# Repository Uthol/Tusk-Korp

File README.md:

# Tusk Korp
Repo for all of my keyboard designs.

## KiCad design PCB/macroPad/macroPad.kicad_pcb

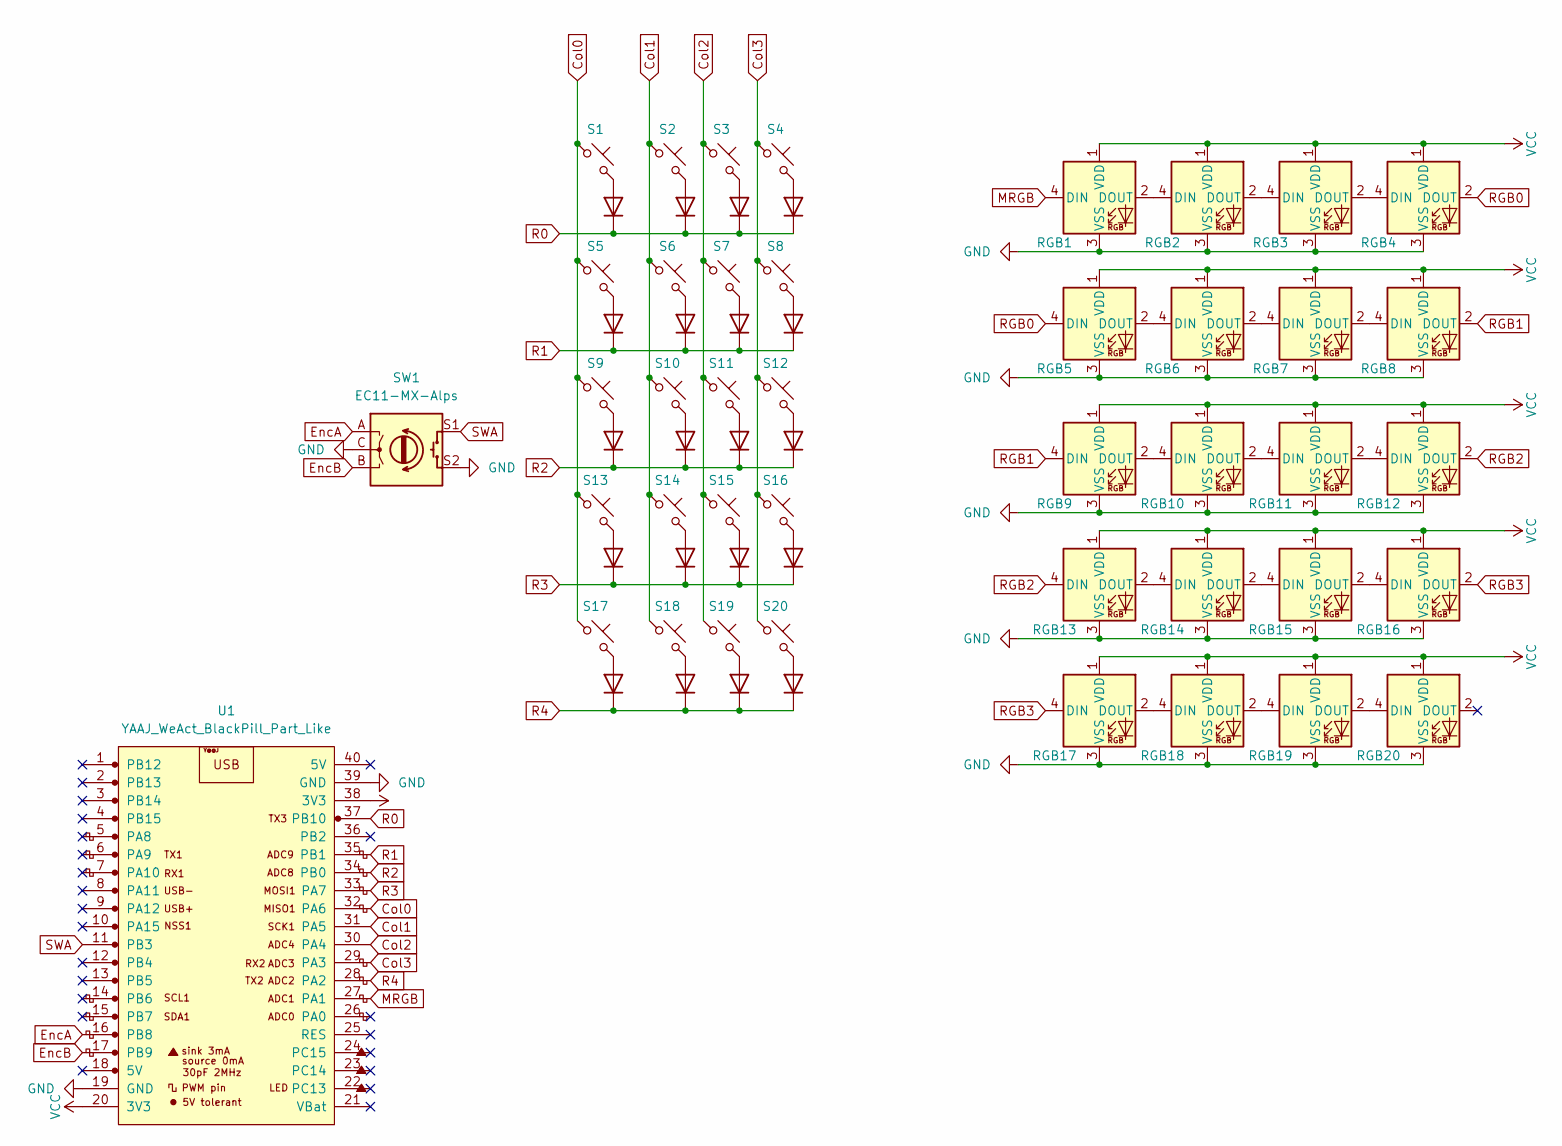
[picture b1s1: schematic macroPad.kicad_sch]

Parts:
D1, D2, D3, D4, D5, D6, D7, D8, D9, D10, D11, D12, D13, D14, D15, D16, D17, D18, D19, D20: 1N4148; D_DO-35_SOD27_P7.62mm_Horizontal
RGB1, RGB2, RGB3, RGB4, RGB5, RGB6, RGB7, RGB8, RGB9, RGB10, RGB11, RGB12, RGB13, RGB14, RGB15, RGB16, RGB17, RGB18, RGB19, RGB20: LED_WS2812B; LED_SK6812MINI
S1, S2, S3, S4, S5, S6, S7, S8, S9, S10, S11, S12, S13, S14, S15, S16, S17, S18, S19, S20: Keyswitch; SW_Cherry_MX_PCB_1.00u
SW1: EC11-MX-Alps; RotaryEncoder_Alps_EC11E-Switch_Vertical_H20mm
U1: YAAJ_WeAct_BlackPill_Part_Like; YAAJ_WeAct_BlackPill_2

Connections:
Col0: S1.1, S5.1, S9.1, S13.1, S17.1, U1.32 (PA6)
Col1: S2.1, S6.1, S10.1, S14.1, S18.1, U1.31 (PA5)
Col2: S3.1, S7.1, S11.1, S15.1, S19.1, U1.30 (PA4)
Col3: S4.1, S8.1, S12.1, S16.1, S20.1, U1.29 (PA3)
EncA: SW1.A, U1.16 (PB8)
EncB: SW1.B, U1.17 (PB9)
GND: RGB1.3 (VSS), RGB2.3 (VSS), RGB3.3 (VSS), RGB4.3 (VSS), RGB5.3 (VSS), RGB6.3 (VSS), RGB7.3 (VSS), RGB8.3 (VSS), RGB9.3 (VSS), RGB10.3 (VSS), RGB11.3 (VSS), RGB12.3 (VSS), RGB13.3 (VSS), RGB14.3 (VSS), RGB15.3 (VSS), RGB16.3 (VSS), RGB17.3 (VSS), RGB18.3 (VSS), RGB19.3 (VSS), RGB20.3 (VSS), SW1.C, SW1.S2, U1.19 (GND), U1.39 (GND)
MRGB: RGB1.4 (DIN), U1.27 (PA1)
unnamed: D1.2 (A), S1.2
unnamed: D2.2 (A), S2.2
unnamed: D3.2 (A), S3.2
unnamed: D4.2 (A), S4.2
unnamed: D5.2 (A), S5.2
unnamed: D6.2 (A), S6.2
unnamed: D7.2 (A), S7.2
unnamed: D8.2 (A), S8.2
unnamed: D9.2 (A), S9.2
unnamed: D10.2 (A), S10.2
unnamed: D11.2 (A), S11.2
unnamed: D12.2 (A), S12.2
unnamed: D13.2 (A), S13.2
unnamed: D14.2 (A), S14.2
unnamed: D15.2 (A), S15.2
unnamed: D16.2 (A), S16.2
unnamed: D17.2 (A), S17.2
unnamed: D18.2 (A), S18.2
unnamed: D19.2 (A), S19.2
unnamed: D20.2 (A), S20.2
unnamed: RGB1.2 (DOUT), RGB2.4 (DIN)
unnamed: RGB2.2 (DOUT), RGB3.4 (DIN)
unnamed: RGB3.2 (DOUT), RGB4.4 (DIN)
unnamed: RGB5.2 (DOUT), RGB6.4 (DIN)
unnamed: RGB6.2 (DOUT), RGB7.4 (DIN)
unnamed: RGB7.2 (DOUT), RGB8.4 (DIN)
unnamed: RGB9.2 (DOUT), RGB10.4 (DIN)
unnamed: RGB10.2 (DOUT), RGB11.4 (DIN)
unnamed: RGB11.2 (DOUT), RGB12.4 (DIN)
unnamed: RGB13.2 (DOUT), RGB14.4 (DIN)
unnamed: RGB14.2 (DOUT), RGB15.4 (DIN)
unnamed: RGB15.2 (DOUT), RGB16.4 (DIN)
unnamed: RGB17.2 (DOUT), RGB18.4 (DIN)
unnamed: RGB18.2 (DOUT), RGB19.4 (DIN)
unnamed: RGB19.2 (DOUT), RGB20.4 (DIN)
R0: D1.1 (K), D2.1 (K), D3.1 (K), D4.1 (K), U1.37 (PB10)
R1: D5.1 (K), D6.1 (K), D7.1 (K), D8.1 (K), U1.35 (PB1)
R2: D9.1 (K), D10.1 (K), D11.1 (K), D12.1 (K), U1.34 (PB0)
R3: D13.1 (K), D14.1 (K), D15.1 (K), D16.1 (K), U1.33 (PA7)
R4: D17.1 (K), D18.1 (K), D19.1 (K), D20.1 (K), U1.28 (PA2)
RGB0: RGB4.2 (DOUT), RGB5.4 (DIN)
RGB1: RGB8.2 (DOUT), RGB9.4 (DIN)
RGB2: RGB12.2 (DOUT), RGB13.4 (DIN)
RGB3: RGB16.2 (DOUT), RGB17.4 (DIN)
SWA: SW1.S1 (1), U1.11 (PB3)
VCC: RGB1.1 (VDD), RGB2.1 (VDD), RGB3.1 (VDD), RGB4.1 (VDD), RGB5.1 (VDD), RGB6.1 (VDD), RGB7.1 (VDD), RGB8.1 (VDD), RGB9.1 (VDD), RGB10.1 (VDD), RGB11.1 (VDD), RGB12.1 (VDD), RGB13.1 (VDD), RGB14.1 (VDD), RGB15.1 (VDD), RGB16.1 (VDD), RGB17.1 (VDD), RGB18.1 (VDD), RGB19.1 (VDD), RGB20.1 (VDD), U1.20 (3V3), U1.38 (3V3)

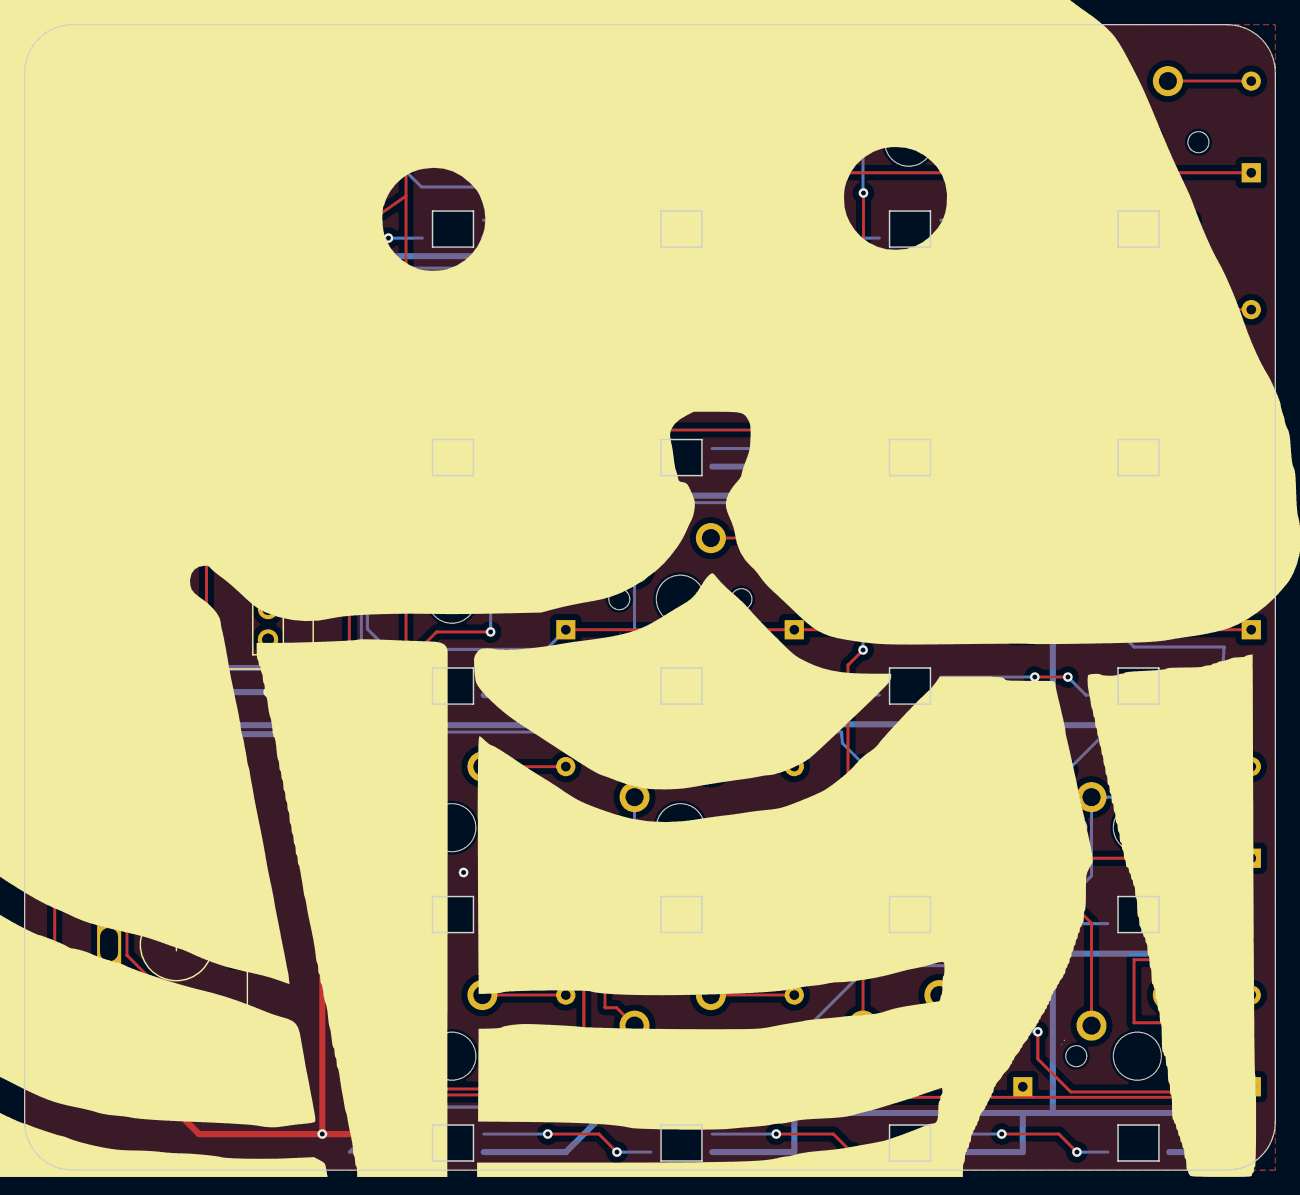
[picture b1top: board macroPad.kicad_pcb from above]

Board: 2 copper layers, 104.0 x 95.2 mm, 62 parts (0 on the bottom side), 54 nets.

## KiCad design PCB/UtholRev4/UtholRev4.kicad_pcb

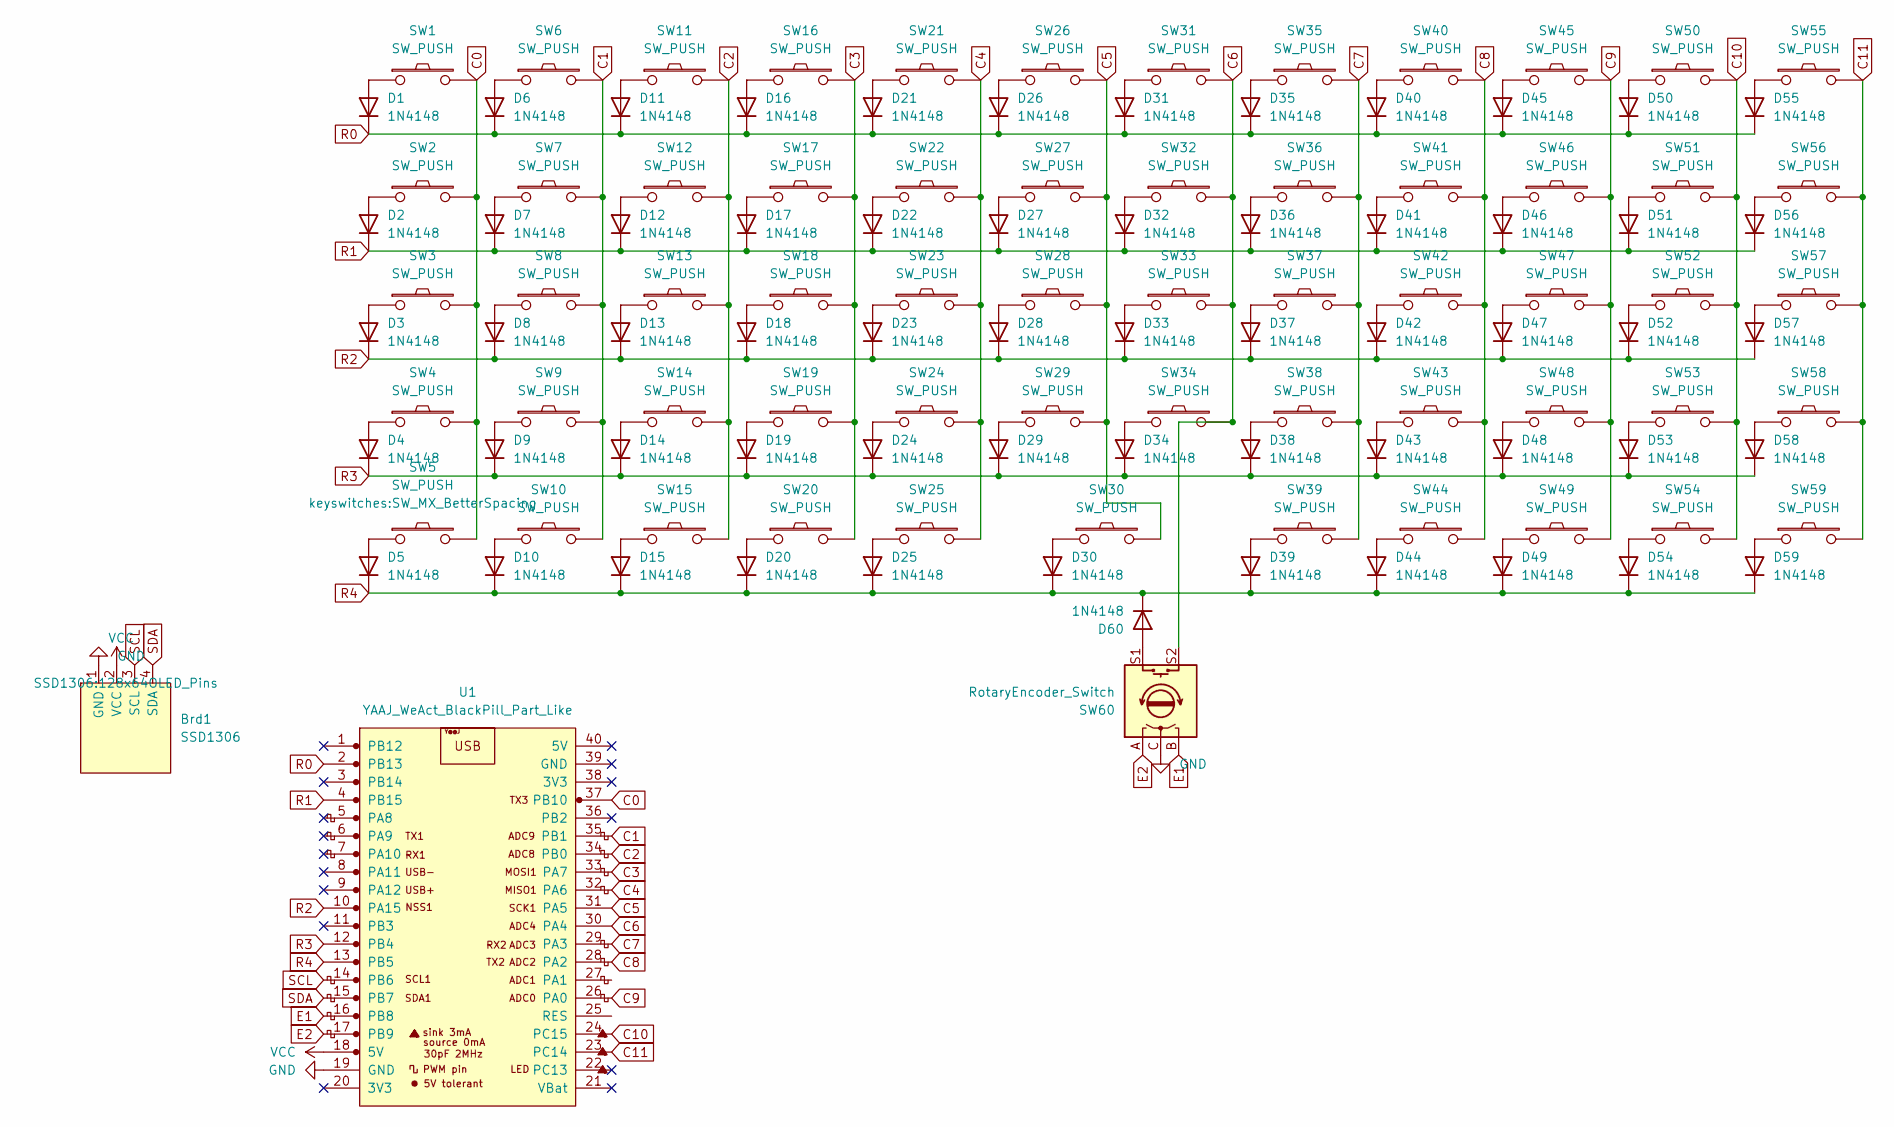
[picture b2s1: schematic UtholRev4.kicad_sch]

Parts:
Brd1: SSD1306; 128x64OLED_Pins
D1, D2, D3, D4, D5, D6, D7, D8, D9, D10, D11, D12, D13, D14, D15, D16, D17, D18, D19, D20, D21, D22, D23, D24, D25, D26, D27, D28, D29, D30, D31, D32, D33, D34, D35, D36, D37, D38, D39, D40, D41, D42, D43, D44, D45, D46, D47, D48, D49, D50, D51, D52, D53, D54, D55, D56, D57, D58, D59, D60: 1N4148; D_DO-35_SOD27_P7.62mm_Horizontal
SW1, SW2, SW3, SW4, SW5, SW6, SW7, SW8, SW9, SW10, SW11, SW12, SW13, SW14, SW15, SW16, SW17, SW18, SW19, SW20, SW21, SW22, SW23, SW24, SW25, SW26, SW27, SW28, SW29, SW30, SW31, SW32, SW33, SW34, SW35, SW36, SW37, SW38, SW39, SW40, SW41, SW42, SW43, SW44, SW45, SW46, SW47, SW48, SW49, SW50, SW51, SW52, SW53, SW54, SW55, SW56, SW57, SW58, SW59: SW_PUSH; SW_MX_BetterSpacing
SW60: RotaryEncoder_Switch; RotaryEncoder_Alps_EC11E-Switch_Vertical_H20mm
U1: YAAJ_WeAct_BlackPill_Part_Like; YAAJ_WeAct_BlackPill_2

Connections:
C0: SW1.2, SW2.2, SW3.2, SW4.2, SW5.2, U1.37 (PB10)
C1: SW6.2, SW7.2, SW8.2, SW9.2, SW10.2, U1.35 (PB1)
C2: SW11.2, SW12.2, SW13.2, SW14.2, SW15.2, U1.34 (PB0)
C3: SW16.2, SW17.2, SW18.2, SW19.2, SW20.2, U1.33 (PA7)
C4: SW21.2, SW22.2, SW23.2, SW24.2, SW25.2, U1.32 (PA6)
C5: SW26.2, SW27.2, SW28.2, SW29.2, SW30.2, U1.31 (PA5)
C6: SW31.2, SW32.2, SW33.2, SW34.2, SW60.S2, U1.30 (PA4)
C7: SW35.2, SW36.2, SW37.2, SW38.2, SW39.2, U1.29 (PA3)
C8: SW40.2, SW41.2, SW42.2, SW43.2, SW44.2, U1.28 (PA2)
C9: SW45.2, SW46.2, SW47.2, SW48.2, SW49.2, U1.26 (PA0)
C10: SW50.2, SW51.2, SW52.2, SW53.2, SW54.2, U1.24 (PC15)
C11: SW55.2, SW56.2, SW57.2, SW58.2, SW59.2, U1.23 (PC14)
E1: SW60.B, U1.16 (PB8)
E2: SW60.A, U1.17 (PB9)
GND: Brd1.1 (GND), SW60.C, U1.19 (GND)
unnamed: D1.2 (A), SW1.1
unnamed: D2.2 (A), SW2.1
unnamed: D3.2 (A), SW3.1
unnamed: D4.2 (A), SW4.1
unnamed: D5.2 (A), SW5.1
unnamed: D6.2 (A), SW6.1
unnamed: D7.2 (A), SW7.1
unnamed: D8.2 (A), SW8.1
unnamed: D9.2 (A), SW9.1
unnamed: D10.2 (A), SW10.1
unnamed: D11.2 (A), SW11.1
unnamed: D12.2 (A), SW12.1
unnamed: D13.2 (A), SW13.1
unnamed: D14.2 (A), SW14.1
unnamed: D15.2 (A), SW15.1
unnamed: D16.2 (A), SW16.1
unnamed: D17.2 (A), SW17.1
unnamed: D18.2 (A), SW18.1
unnamed: D19.2 (A), SW19.1
unnamed: D20.2 (A), SW20.1
unnamed: D21.2 (A), SW21.1
unnamed: D22.2 (A), SW22.1
unnamed: D23.2 (A), SW23.1
unnamed: D24.2 (A), SW24.1
unnamed: D25.2 (A), SW25.1
unnamed: D26.2 (A), SW26.1
unnamed: D27.2 (A), SW27.1
unnamed: D28.2 (A), SW28.1
unnamed: D29.2 (A), SW29.1
unnamed: D30.2 (A), SW30.1
unnamed: D31.2 (A), SW31.1
unnamed: D32.2 (A), SW32.1
unnamed: D33.2 (A), SW33.1
unnamed: D34.2 (A), SW34.1
unnamed: D35.2 (A), SW35.1
unnamed: D36.2 (A), SW36.1
unnamed: D37.2 (A), SW37.1
unnamed: D38.2 (A), SW38.1
unnamed: D39.2 (A), SW39.1
unnamed: D40.2 (A), SW40.1
unnamed: D41.2 (A), SW41.1
unnamed: D42.2 (A), SW42.1
unnamed: D43.2 (A), SW43.1
unnamed: D44.2 (A), SW44.1
unnamed: D45.2 (A), SW45.1
unnamed: D46.2 (A), SW46.1
unnamed: D47.2 (A), SW47.1
unnamed: D48.2 (A), SW48.1
unnamed: D49.2 (A), SW49.1
unnamed: D50.2 (A), SW50.1
unnamed: D51.2 (A), SW51.1
unnamed: D52.2 (A), SW52.1
unnamed: D53.2 (A), SW53.1
unnamed: D54.2 (A), SW54.1
unnamed: D55.2 (A), SW55.1
unnamed: D56.2 (A), SW56.1
unnamed: D57.2 (A), SW57.1
unnamed: D58.2 (A), SW58.1
unnamed: D59.2 (A), SW59.1
unnamed: D60.2 (A), SW60.S1
R0: D1.1 (K), D6.1 (K), D11.1 (K), D16.1 (K), D21.1 (K), D26.1 (K), D31.1 (K), D35.1 (K), D40.1 (K), D45.1 (K), D50.1 (K), D55.1 (K), U1.2 (PB13)
R1: D2.1 (K), D7.1 (K), D12.1 (K), D17.1 (K), D22.1 (K), D27.1 (K), D32.1 (K), D36.1 (K), D41.1 (K), D46.1 (K), D51.1 (K), D56.1 (K), U1.4 (PB15)
R2: D3.1 (K), D8.1 (K), D13.1 (K), D18.1 (K), D23.1 (K), D28.1 (K), D33.1 (K), D37.1 (K), D42.1 (K), D47.1 (K), D52.1 (K), D57.1 (K), U1.10 (PA15)
R3: D4.1 (K), D9.1 (K), D14.1 (K), D19.1 (K), D24.1 (K), D29.1 (K), D34.1 (K), D38.1 (K), D43.1 (K), D48.1 (K), D53.1 (K), D58.1 (K), U1.12 (PB4)
R4: D5.1 (K), D10.1 (K), D15.1 (K), D20.1 (K), D25.1 (K), D30.1 (K), D39.1 (K), D44.1 (K), D49.1 (K), D54.1 (K), D59.1 (K), D60.1 (K), U1.13 (PB5)
SCL: Brd1.3 (SCL), U1.14 (PB6)
SDA: Brd1.4 (SDA), U1.15 (PB7)
VCC: Brd1.2 (VCC), U1.18 (5V)

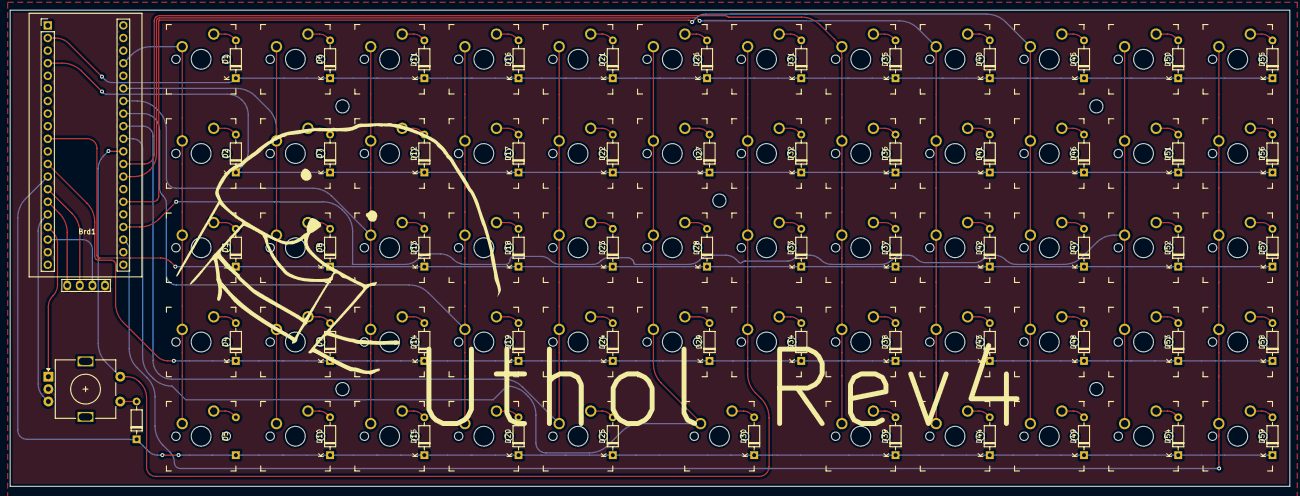
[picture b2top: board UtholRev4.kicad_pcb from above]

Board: 2 copper layers, 258.0 x 96.0 mm, 122 parts (0 on the bottom side), 83 nets.

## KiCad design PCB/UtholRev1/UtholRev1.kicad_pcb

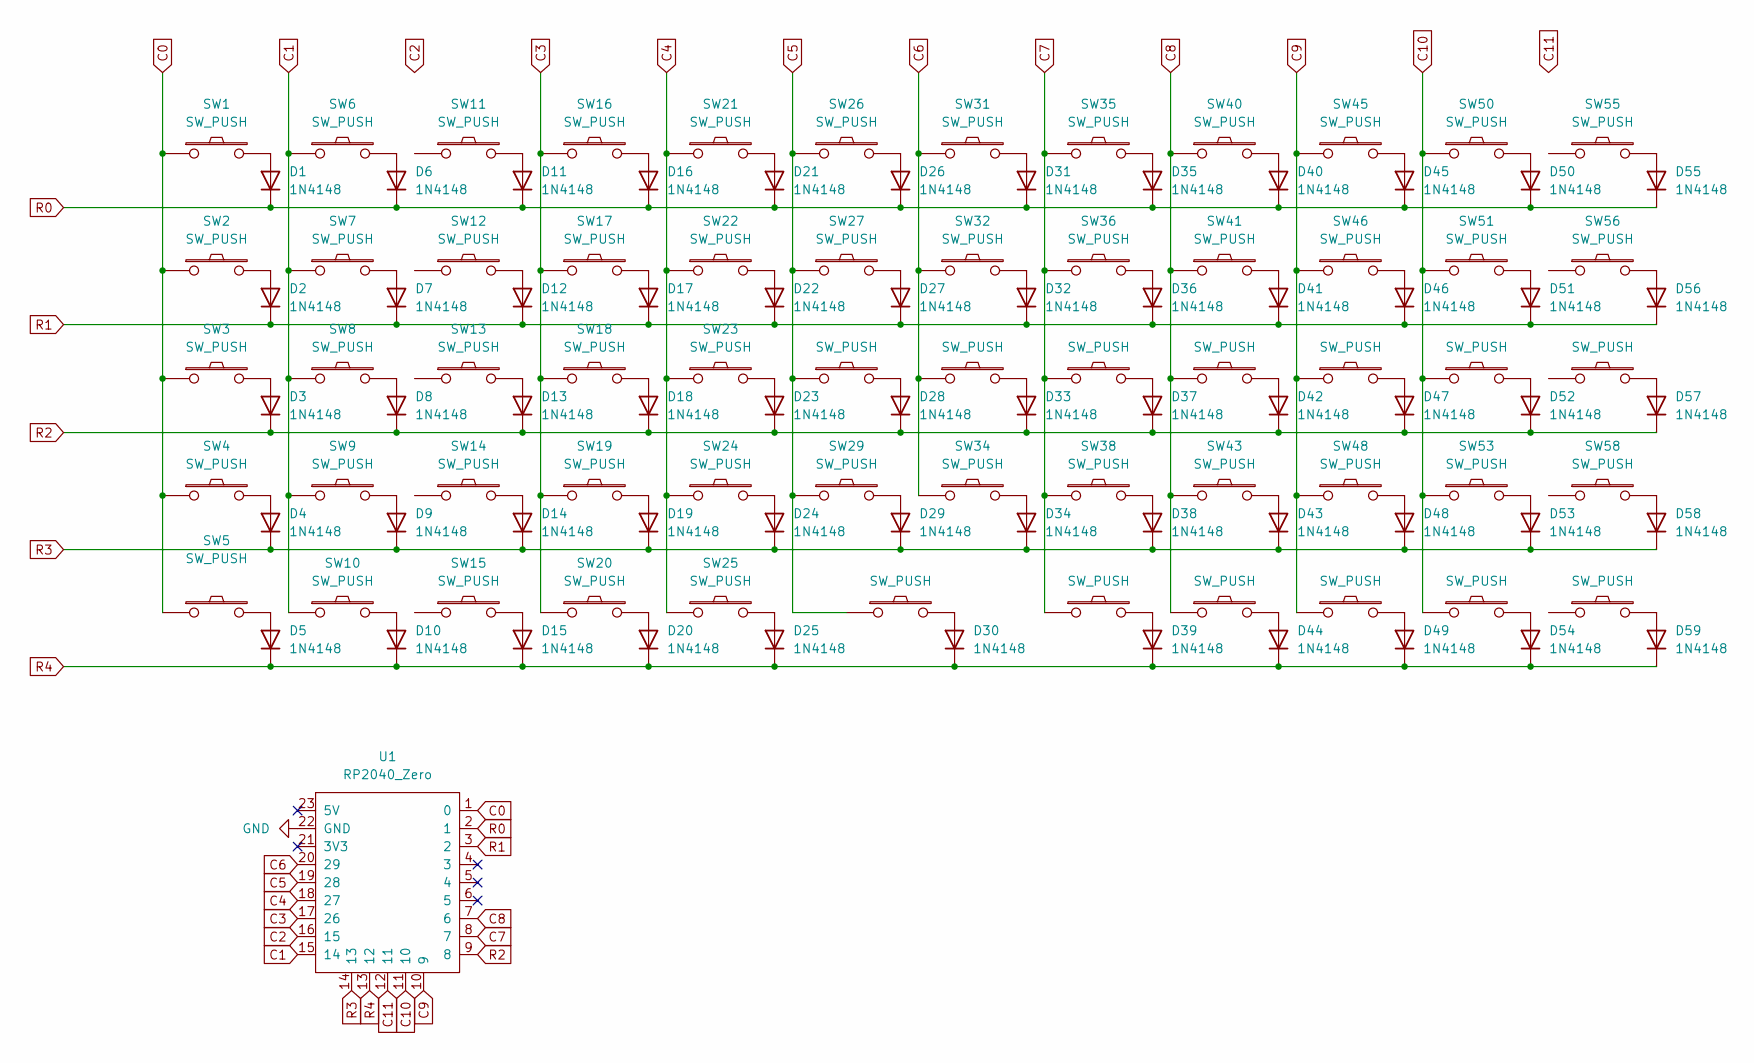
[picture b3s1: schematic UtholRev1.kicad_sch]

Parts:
D1, D2, D3, D4, D5, D6, D7, D8, D9, D10, D11, D12, D13, D14, D15, D16, D17, D18, D19, D20, D21, D22, D23, D24, D25, D26, D27, D28, D29, D30, D31, D32, D33, D34, D35, D36, D37, D38, D39, D40, D41, D42, D43, D44, D45, D46, D47, D48, D49, D50, D51, D52, D53, D54, D55, D56, D57, D58, D59: 1N4148; Diode_SOD-123
SW1, SW2, SW3, SW4, SW5, SW6, SW7, SW8, SW9, SW10, SW11, SW12, SW13, SW14, SW15, SW16, SW17, SW18, SW19, SW20, SW21, SW22, SW23, SW24, SW25, SW26, SW27, SW28, SW29, SW30, SW31, SW32, SW33, SW34, SW35, SW36, SW37, SW38, SW39, SW40, SW41, SW42, SW43, SW44, SW45, SW46, SW47, SW48, SW49, SW50, SW51, SW52, SW53, SW54, SW55, SW56, SW57, SW58, SW59: SW_PUSH; MX_PCB_1.00u
U1: RP2040_Zero; RP2040_Zero_Flipped

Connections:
C0: SW1.1, SW2.1, SW3.1, SW4.1, SW5.1, U1.1 (0)
C1: SW6.1, SW7.1, SW8.1, SW9.1, SW10.1, U1.15 (14)
C2: U1.16 (15)
C3: SW16.1, SW17.1, SW18.1, SW19.1, SW20.1, U1.17 (26)
C4: SW21.1, SW22.1, SW23.1, SW24.1, SW25.1, U1.18 (27)
C5: SW26.1, SW27.1, SW28.1, SW29.1, SW30.1, U1.19 (28)
C6: SW31.1, SW32.1, SW33.1, SW34.1, U1.20 (29)
C7: SW35.1, SW36.1, SW37.1, SW38.1, SW39.1, U1.8 (7)
C8: SW40.1, SW41.1, SW42.1, SW43.1, SW44.1, U1.7 (6)
C9: SW45.1, SW46.1, SW47.1, SW48.1, SW49.1, U1.10 (9)
C10: SW50.1, SW51.1, SW52.1, SW53.1, SW54.1, U1.11 (10)
C11: U1.12 (11)
GND: U1.22 (GND)
unnamed: D1.2 (A), SW1.2
unnamed: D2.2 (A), SW2.2
unnamed: D3.2 (A), SW3.2
unnamed: D4.2 (A), SW4.2
unnamed: D5.2 (A), SW5.2
unnamed: D6.2 (A), SW6.2
unnamed: D7.2 (A), SW7.2
unnamed: D8.2 (A), SW8.2
unnamed: D9.2 (A), SW9.2
unnamed: D10.2 (A), SW10.2
unnamed: D11.2 (A), SW11.2
unnamed: D12.2 (A), SW12.2
unnamed: D13.2 (A), SW13.2
unnamed: D14.2 (A), SW14.2
unnamed: D15.2 (A), SW15.2
unnamed: D16.2 (A), SW16.2
unnamed: D17.2 (A), SW17.2
unnamed: D18.2 (A), SW18.2
unnamed: D19.2 (A), SW19.2
unnamed: D20.2 (A), SW20.2
unnamed: D21.2 (A), SW21.2
unnamed: D22.2 (A), SW22.2
unnamed: D23.2 (A), SW23.2
unnamed: D24.2 (A), SW24.2
unnamed: D25.2 (A), SW25.2
unnamed: D26.2 (A), SW26.2
unnamed: D27.2 (A), SW27.2
unnamed: D28.2 (A), SW28.2
unnamed: D29.2 (A), SW29.2
unnamed: D30.2 (A), SW30.2
unnamed: D31.2 (A), SW31.2
unnamed: D32.2 (A), SW32.2
unnamed: D33.2 (A), SW33.2
unnamed: D34.2 (A), SW34.2
unnamed: D35.2 (A), SW35.2
unnamed: D36.2 (A), SW36.2
unnamed: D37.2 (A), SW37.2
unnamed: D38.2 (A), SW38.2
unnamed: D39.2 (A), SW39.2
unnamed: D40.2 (A), SW40.2
unnamed: D41.2 (A), SW41.2
unnamed: D42.2 (A), SW42.2
unnamed: D43.2 (A), SW43.2
unnamed: D44.2 (A), SW44.2
unnamed: D45.2 (A), SW45.2
unnamed: D46.2 (A), SW46.2
unnamed: D47.2 (A), SW47.2
unnamed: D48.2 (A), SW48.2
unnamed: D49.2 (A), SW49.2
unnamed: D50.2 (A), SW50.2
unnamed: D51.2 (A), SW51.2
unnamed: D52.2 (A), SW52.2
unnamed: D53.2 (A), SW53.2
unnamed: D54.2 (A), SW54.2
unnamed: D55.2 (A), SW55.2
unnamed: D56.2 (A), SW56.2
unnamed: D57.2 (A), SW57.2
unnamed: D58.2 (A), SW58.2
unnamed: D59.2 (A), SW59.2
R0: D1.1 (K), D6.1 (K), D11.1 (K), D16.1 (K), D21.1 (K), D26.1 (K), D31.1 (K), D35.1 (K), D40.1 (K), D45.1 (K), D50.1 (K), D55.1 (K), U1.2 (1)
R1: D2.1 (K), D7.1 (K), D12.1 (K), D17.1 (K), D22.1 (K), D27.1 (K), D32.1 (K), D36.1 (K), D41.1 (K), D46.1 (K), D51.1 (K), D56.1 (K), U1.3 (2)
R2: D3.1 (K), D8.1 (K), D13.1 (K), D18.1 (K), D23.1 (K), D28.1 (K), D33.1 (K), D37.1 (K), D42.1 (K), D47.1 (K), D52.1 (K), D57.1 (K), U1.9 (8)
R3: D4.1 (K), D9.1 (K), D14.1 (K), D19.1 (K), D24.1 (K), D29.1 (K), D34.1 (K), D38.1 (K), D43.1 (K), D48.1 (K), D53.1 (K), D58.1 (K), U1.14 (13)
R4: D5.1 (K), D10.1 (K), D15.1 (K), D20.1 (K), D25.1 (K), D30.1 (K), D39.1 (K), D44.1 (K), D49.1 (K), D54.1 (K), D59.1 (K), U1.13 (12)

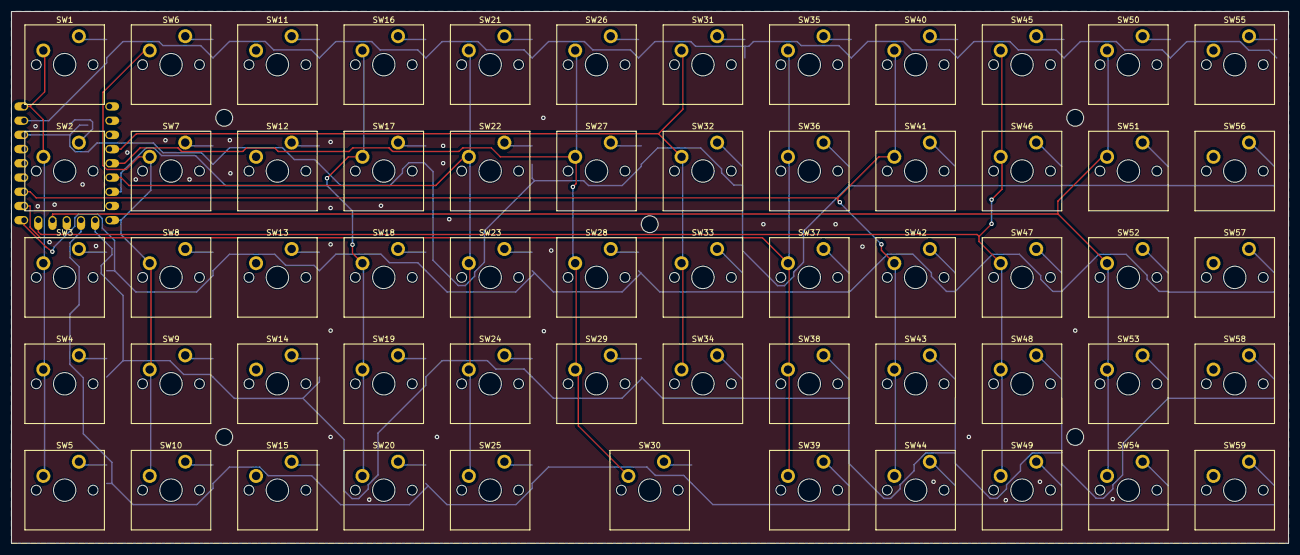
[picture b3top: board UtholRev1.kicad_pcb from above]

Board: 2 copper layers, 228.1 x 95.0 mm, 119 parts (0 on the bottom side), 74 nets.

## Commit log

2023-10-30 update readme and basic folder structure
2023-10-30 update folders
2023-10-30 test
2023-10-30 Delete PCB/StakaLow/StakaLow-backups directory
    Delete PCB/StakaLow/StakaLow-backups directory
2023-10-30 add macropad
